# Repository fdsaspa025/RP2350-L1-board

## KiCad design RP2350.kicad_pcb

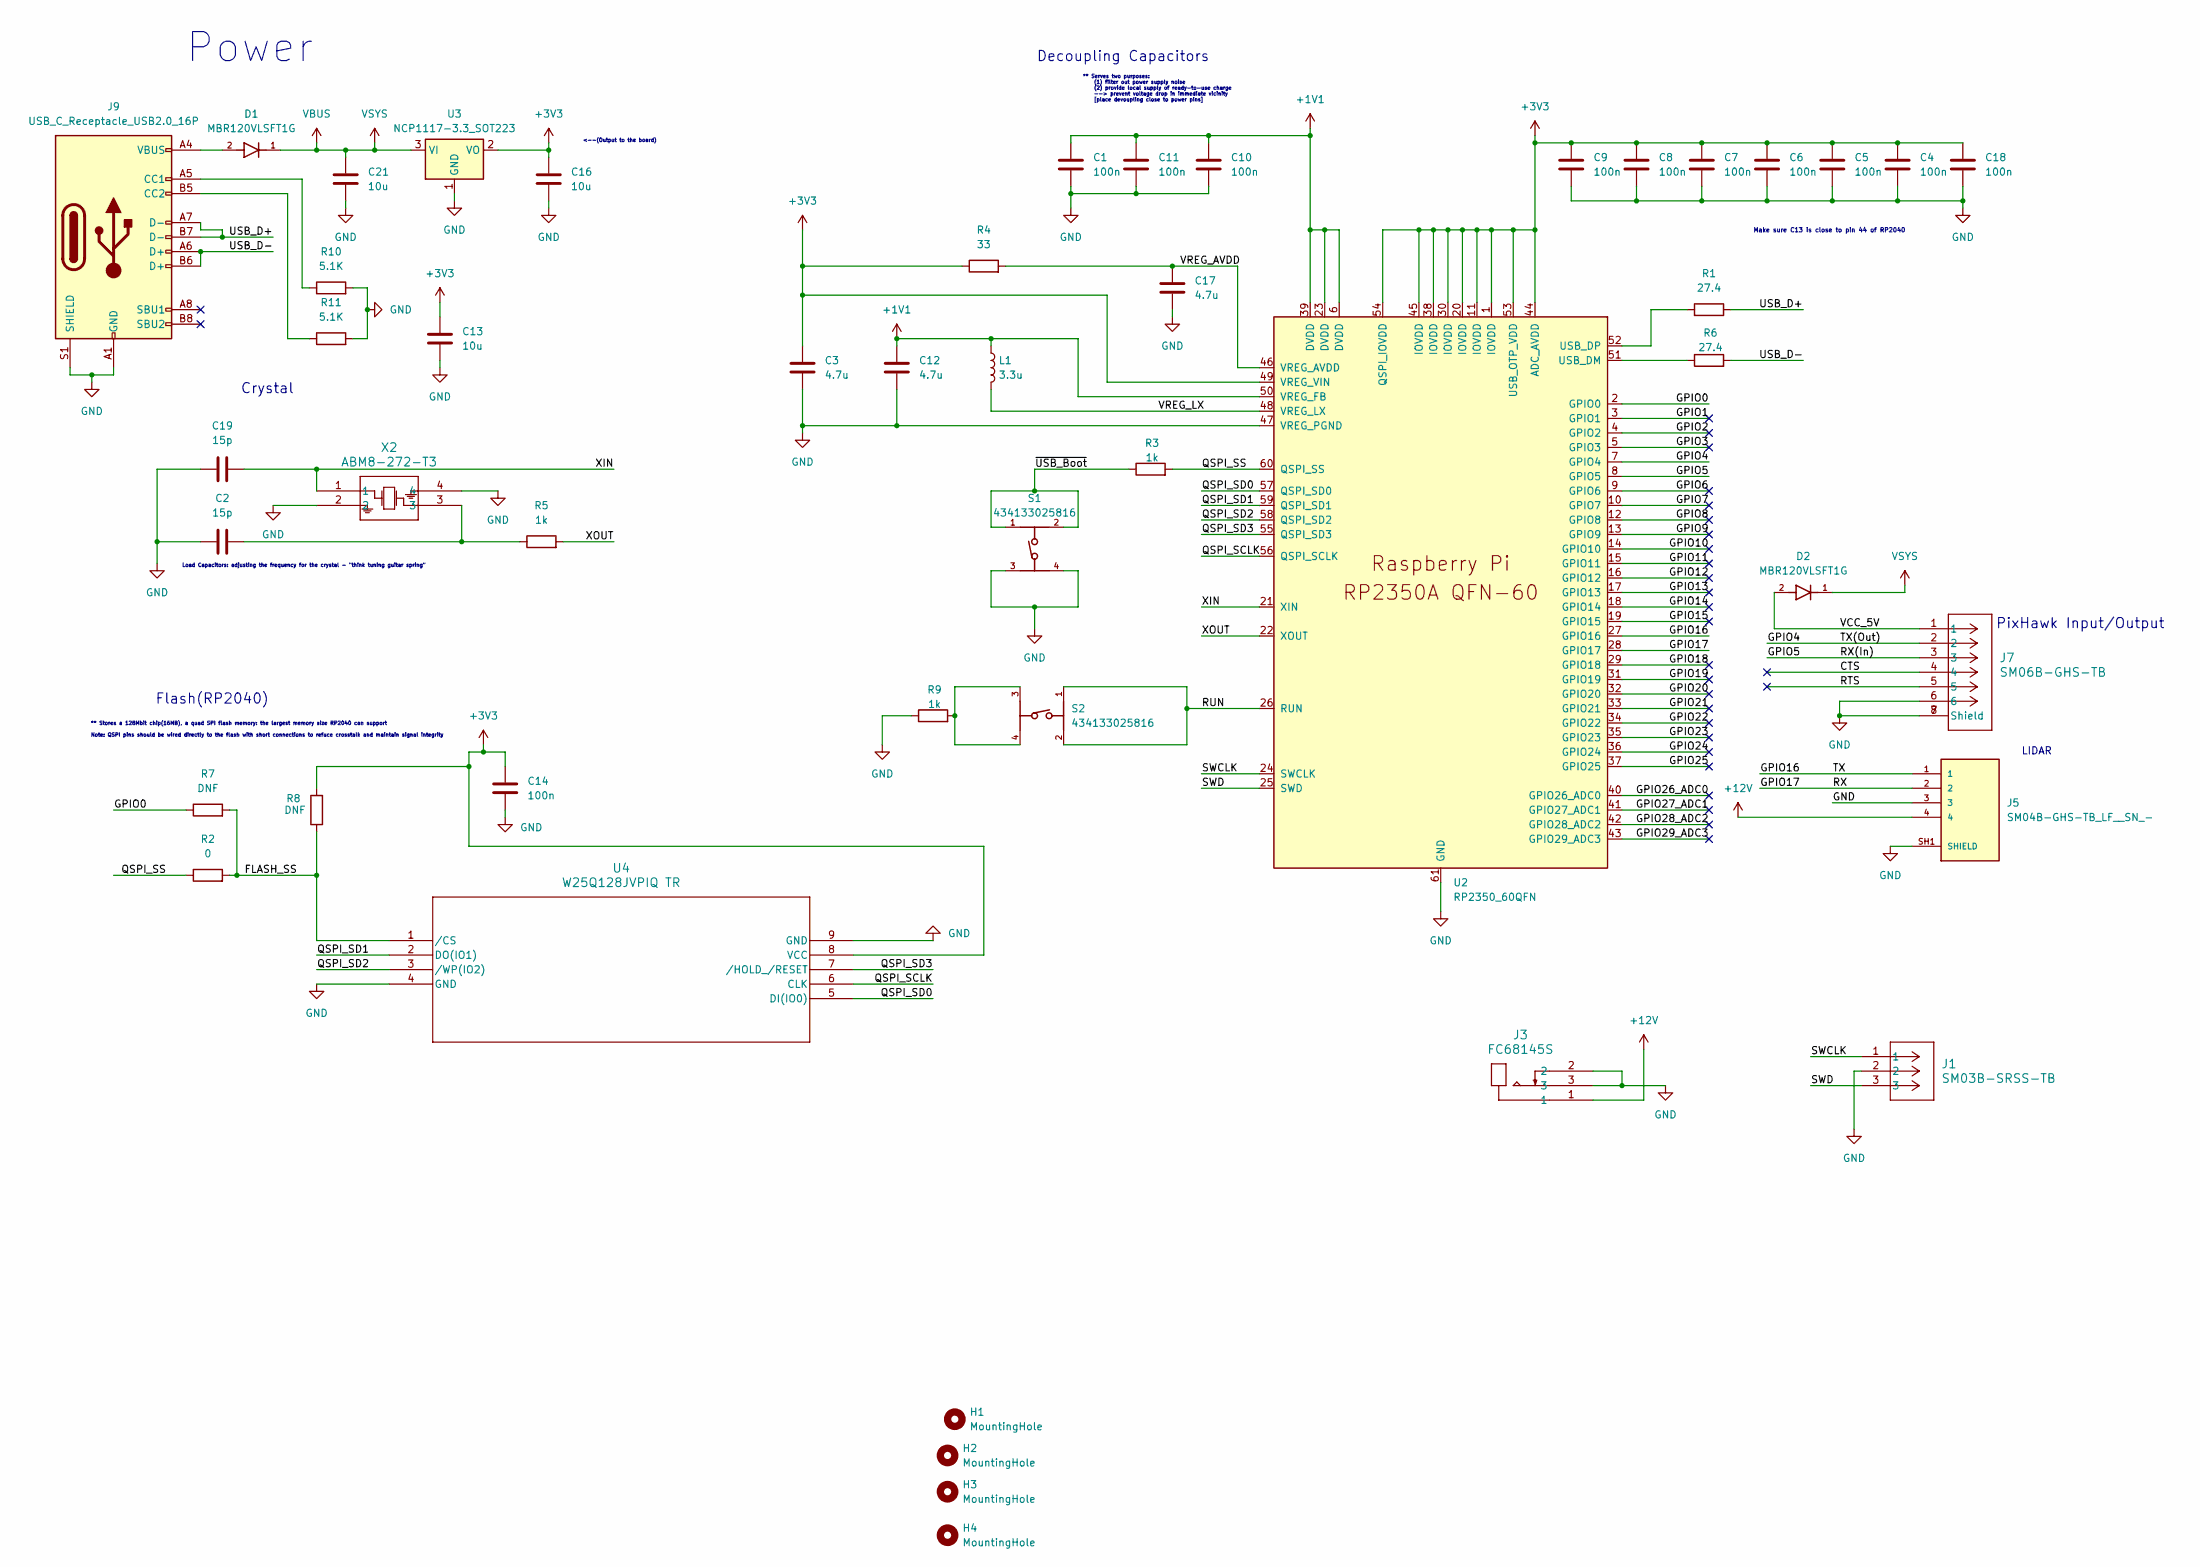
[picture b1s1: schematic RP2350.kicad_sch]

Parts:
C1, C4, C5, C6, C7, C8, C9, C10, C11, C14, C18: 100n; C_0402_1005Metric
C2, C19: 15p; C_0402_1005Metric
C3, C12: 4.7u; C_0603_1608Metric
C13, C16, C21: 10u; C_0805_2012Metric
C17: 4.7u; C_0402_1005Metric
D1, D2: MBR120VLSFT1G; DIOM3616X98N; PARTREV 5/10/2013
H1, H2, H3, H4: MountingHole; MountingHole_2.7mm_M2.5_Pad_TopBottom
J1: SM03B-SRSS-TB; CONN_SM03B-SRSS-TB_JST
J3: FC68145S; FC68145S_CLF
J5: SM04B-GHS-TB_LF__SN_-; JST_SM04B-GHS-TB_LF__SN_-; PARTREV NA
J7: SM06B-GHS-TB; CONN_SM06B-GHS-TB_JST
J9: USB_C_Receptacle_USB2.0_16P; USB_C_Receptacle_GCT_USB4105-xx-A_16P_TopMnt_Horizontal
L1: 3.3u; L_0603_1608Metric
R1, R6: 27.4; R_0402_1005Metric
R2: 0; R_0402_1005Metric
R3, R5, R9: 1k; R_0402_1005Metric
R4: 33; R_0402_1005Metric
R7, R8: DNF; R_0402_1005Metric
R10, R11: 5.1K; R_0402_1005Metric
S1, S2: 434133025816
U2: RP2350_60QFN; RP2350-QFN-60-1EP_7x7_P0.4mm_EP3.4x3.4mm_ThermalVias
U3: NCP1117-3.3_SOT223; SOT-223-3_TabPin2
U4: W25Q128JVPIQ TR; WSON-8_6X5_WIN
X2: ABM8-272-T3; ABM8-272-T3_ABR

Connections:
+1V1: C1.1, C10.1, C11.1, C12.1, L1.1, U2.6 (DVDD), U2.23 (DVDD), U2.39 (DVDD), U2.50 (VREG_FB)
+3V3: C3.1, C4.1, C5.1, C6.1, C7.1, C8.1, C9.1, C13.1, C14.1, C16.1, C18.1, R4.1, R8.2, U2.1 (IOVDD), U2.11 (IOVDD), U2.20 (IOVDD), U2.30 (IOVDD), U2.38 (IOVDD), U2.44 (ADC_AVDD), U2.45 (IOVDD), U2.49 (VREG_VIN), U2.53 (USB_OTP_VDD), U2.54 (QSPI_IOVDD), U3.2 (VO), U4.8 (VCC)
+12V: J3.1, J5.4
/CTS: J7.4
/FLASH_SS: R2.2, R7.2, R8.1, U4.1 (/CS)
/GPIO0: R7.1, U2.2 (GPIO0)
/GPIO1: U2.3 (GPIO1)
/GPIO2: U2.4 (GPIO2)
/GPIO3: U2.5 (GPIO3)
/GPIO4: J7.2, U2.7 (GPIO4)
/GPIO5: J7.3, U2.8 (GPIO5)
/GPIO6: U2.9 (GPIO6)
/GPIO7: U2.10 (GPIO7)
/GPIO8: U2.12 (GPIO8)
/GPIO9: U2.13 (GPIO9)
/GPIO10: U2.14 (GPIO10)
/GPIO11: U2.15 (GPIO11)
/GPIO12: U2.16 (GPIO12)
/GPIO13: U2.17 (GPIO13)
/GPIO14: U2.18 (GPIO14)
/GPIO15: U2.19 (GPIO15)
/GPIO16: J5.1, U2.27 (GPIO16)
/GPIO17: J5.2, U2.28 (GPIO17)
/GPIO18: U2.29 (GPIO18)
/GPIO19: U2.31 (GPIO19)
/GPIO20: U2.32 (GPIO20)
/GPIO21: U2.33 (GPIO21)
/GPIO22: U2.34 (GPIO22)
/GPIO23: U2.35 (GPIO23)
/GPIO24: U2.36 (GPIO24)
/GPIO25: U2.37 (GPIO25)
/GPIO26_ADC0: U2.40 (GPIO26_ADC0)
/GPIO27_ADC1: U2.41 (GPIO27_ADC1)
/GPIO28_ADC2: U2.42 (GPIO28_ADC2)
/GPIO29_ADC3: U2.43 (GPIO29_ADC3)
/QSPI_SCLK: U2.56 (QSPI_SCLK), U4.6 (CLK)
/QSPI_SD0: U2.57 (QSPI_SD0), U4.5 (DI(IO0))
/QSPI_SD1: U2.59 (QSPI_SD1), U4.2 (DO(IO1))
/QSPI_SD2: U2.58 (QSPI_SD2), U4.3 (/WP(IO2))
/QSPI_SD3: U2.55 (QSPI_SD3), U4.7 (/HOLD_/RESET)
/QSPI_SS: R2.1, R3.2, U2.60 (QSPI_SS)
/RTS: J7.5
/RUN: S2.1, S2.2, U2.26 (RUN)
/SWCLK: J1.1, U2.24 (SWCLK)
/SWD: J1.3, U2.25 (SWD)
/USB_D+: J9.A7 (D-), J9.B7 (D-), R1.1
/USB_D-: J9.A6 (D+), J9.B6 (D+), R6.2
/VCC_5V: D2.2, J7.1
/VREG_AVDD: C17.1, R4.2, U2.46 (VREG_AVDD)
/VREG_LX: L1.2, U2.48 (VREG_LX)
/XIN: C19.2, U2.21 (XIN), X2.1
/XOUT: R5.2, U2.22 (XOUT)
/~USB_Boot: R3.1, S1.1, S1.2
GND: C1.2, C2.1, C3.2, C4.2, C5.2, C6.2, C7.2, C8.2, C9.2, C10.2, C11.2, C12.2, C13.2, C14.2, C16.2, C17.2, C18.2, C19.1, C21.2, J1.2, J3.2, J3.3, J5.3, J5.SH1 (SHIELD), J5.SH2 (SHIELD), J7.6, J7.7 (Shield), J7.8 (Shield), J9.A1 (GND), J9.A12 (GND), J9.B1 (GND), J9.B12 (GND), J9.S1 (SHIELD), R9.1, R10.2, R11.2, S1.3, S1.4, U2.47 (VREG_PGND), U2.61 (GND), U3.1 (GND), U4.4 (GND), U4.9 (GND), X2.2, X2.4
unnamed: C2.2, R5.1, X2.3
unnamed: D1.2, J9.A4 (VBUS), J9.A9 (VBUS), J9.B4 (VBUS), J9.B9 (VBUS)
unnamed: J9.A5 (CC1), R10.1
unnamed: J9.B5 (CC2), R11.1
unnamed: R9.2, S2.3, S2.4
unnamed: R6.1, U2.51 (USB_DM)
unnamed: R1.2, U2.52 (USB_DP)
VBUS: C21.1, D1.1, D2.1, U3.3 (VI)

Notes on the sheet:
LIDAR
Crystal
Power
Decoupling Capacitors
Make sure C13 is close to pin 44 of RP2040
<--(Output to the board)
Load Capacitors: adjusting the frequency for the crystal - "think tuning guitar spring"
** Stores a 128Mbit chip(16MB), a quad SPI flash memory: the largest memory size RP2040 can support Note: QSPI pins should be wired directly to the flash with short connections to refuce crosstalk and maintain signal integrity
** Serves two purposes: (1) filter out power supply noise (2) provide local supply of ready-to-use charge --> prevent voltage drop in immediate vicinity [place devoupling close to power pins]
Flash(RP2040)
PixHawk Input/Output

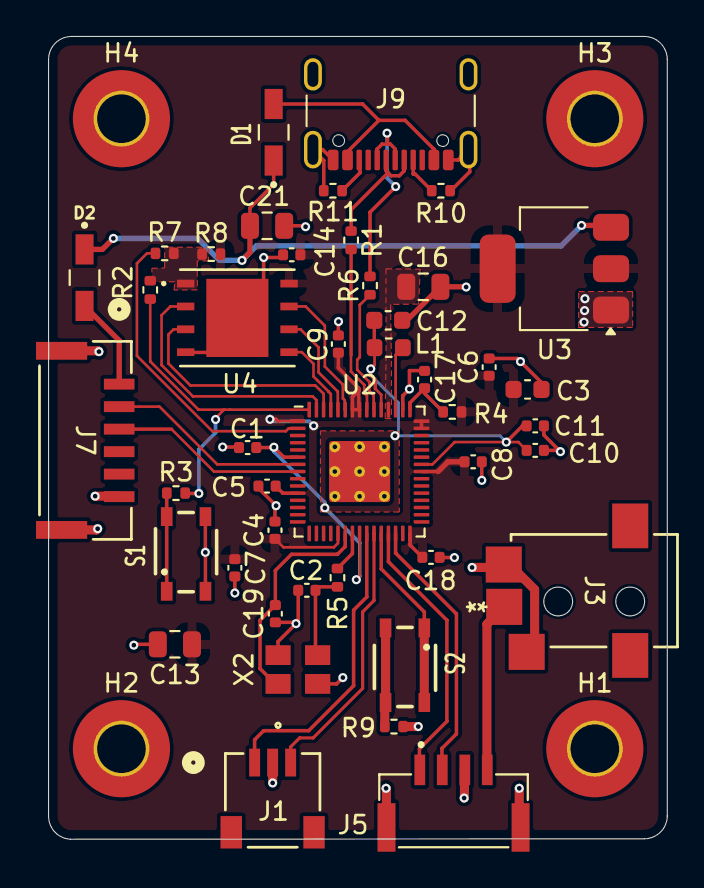
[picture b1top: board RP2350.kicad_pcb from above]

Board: 2 copper layers, 34.4 x 44.6 mm, 48 parts (0 on the bottom side), 35 nets.

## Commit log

2026-02-14 Comment and edit gitignore
2026-02-14 edge edits
